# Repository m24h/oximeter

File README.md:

# oximeter
A small oximeter using MAX30102/STC8G1K08A/0.5-inch-OLED/Phase-Detect algorithm

features:

1. SpO2 detection.
2. Heart beat rate detection.
3. With a USB charging interface.
4. Small and cheap.
5. Compatible with Keil C51 or SDCC

!!!IMPORTANT!!!

First thing:
I made an ergonomic mistake in my design, my original idea was to use a button to turn on the power and the sensor underneath would just fit the finger.
But the excessive pressure affected the blood flowing in the finger, also the results.
I suggest that subsequent developers can modify the PCB and box case, use a toggle switche instead of the button, which can be placed on the side of the case, and place the sensor on the same side of the OLED (Top side), So the users can just touch the sensor surface gently by a finger, that would result in fast and accurate detection results.

Second thing:
Hex file for burning/Downloading is included here, TTL serial port is connected to D+/D- pin of USB charging interface, subsequent developers can also try to download hex file directly using pseudo USB downloading port of STC8G1K08A (ID pin of micro-USB port is required to be connected to GND, but I've never tried, and I heard that there is a certain failure rate).
But STC-ISP V6.90 (the STC official downloading software) has an strange BUG, which will cause straightforward downloading to fail.
In my design, I put const parameters like fonts and some tables into EEPROM area (which is indexed from 0x2000), STC-ISP says "This file is over the valid scope, and the exceeding part has been moved to EEPROM area", which looks as expected, BUT it is not. STC-ISP does not split the hex file at 0x2000, but at 0x1FF9.
The workaround for this strange problem is to manually delete first 7 bytes at "EEPROM Buffer" tab-page on the STC-ISP interface, and "Save Buffer" to a .bin file, and re-load the file using "Open EEPROM file", the burn it.

Other downloading things:
IRC frequency is 22.1184MHz.
Don't enable WDT.
Rest pin is used as I/O port.

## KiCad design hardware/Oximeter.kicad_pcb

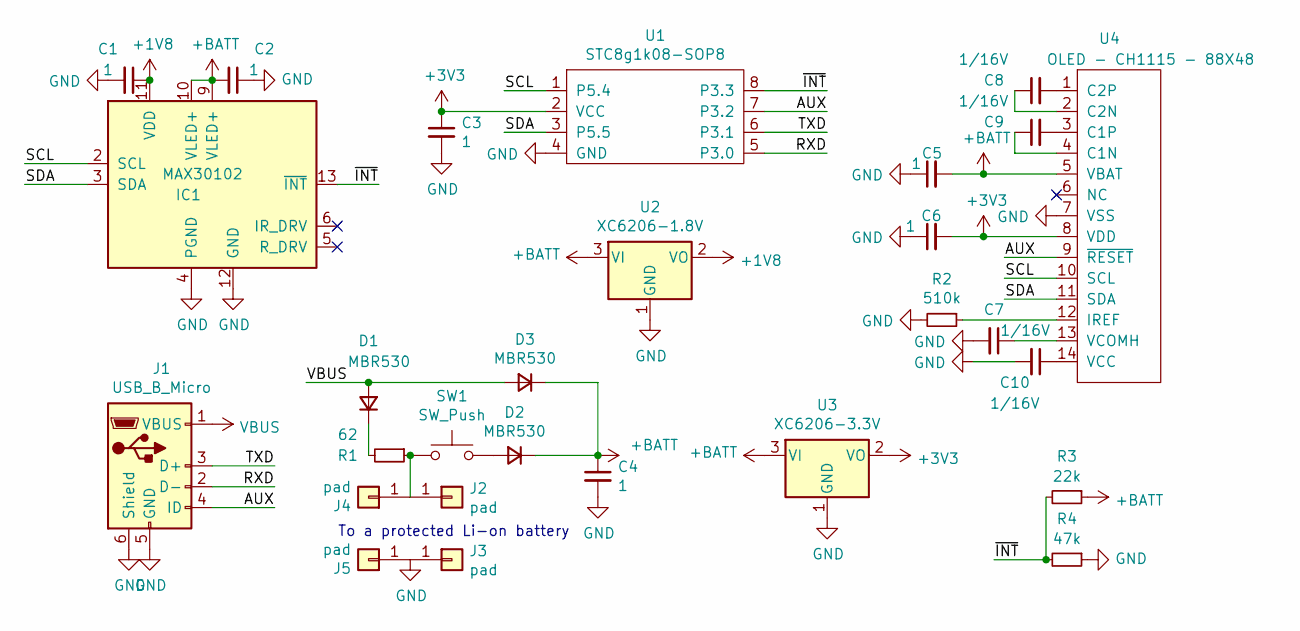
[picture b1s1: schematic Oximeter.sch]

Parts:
C1, C2, C3, C4, C5, C6: 1; C_0603_1608Metric
C7, C8, C9, C10: 1/16V; C_0603_1608Metric
D1, D2, D3: MBR530; D_SOD-123
IC1: MAX30102; Maxim_OLGA-14_3.3x5.6mm_P0.8mm
J1: USB_B_Micro; USB_Micro-B_Molex-105017-0001
J2, J3, J4, J5: pad; Pad-SMD
R1: 62; R_0603_1608Metric
R2: 510k; R_0603_1608Metric
R3: 22k; R_0603_1608Metric
R4: 47k; R_0603_1608Metric
SW1: SW_Push; SW_Push_1P1T_NO_6x6mm_H9.5mm
U1: STC8g1k08-SOP8; SOP-8_3.9x4.9mm_P1.27mm
U2: XC6206-1.8V; SOT-23
U3: XC6206-3.3V; SOT-23
U4: OLED - CH1115 - 88X48; OLED-0.5IN-14PIN

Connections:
+1V8: C1.1, IC1.11 (VDD), U2.2 (VO)
+3V3: C3.1, C6.2, U1.2 (VCC), U3.2 (VO), U4.8 (VDD)
+BATT: C2.2, C4.1, C5.2, D2.1 (K), D3.1 (K), IC1.9 (VLED+), IC1.10 (VLED+), R3.1, U2.3 (VI), U3.3 (VI), U4.5 (VBAT)
/AUX: J1.4 (ID), U1.7 (P3.2), U4.9 (~RESET)
/RXD: J1.2 (D-), U1.5 (P3.0)
/SCL: IC1.2 (SCL), U1.1 (P5.4), U4.10 (SCL)
/SDA: IC1.3 (SDA), U1.3 (P5.5), U4.11 (SDA)
/TXD: J1.3 (D+), U1.6 (P3.1)
/~INT: IC1.13 (~INT), R3.2, R4.2, U1.8 (P3.3)
GND: C1.2, C2.1, C3.2, C4.2, C5.1, C6.1, C7.2, C10.2, IC1.4 (PGND), IC1.12 (GND), J1.5 (GND), J1.6 (Shield), J3.1, J5.1, R2.2, R4.1, U1.4 (GND), U2.1 (GND), U3.1 (GND), U4.7 (VSS)
unnamed: C7.1, U4.13 (VCOMH)
unnamed: C8.1, U4.2 (C2N)
unnamed: C8.2, U4.1 (C2P)
unnamed: C9.1, U4.4 (C1N)
unnamed: C9.2, U4.3 (C1P)
unnamed: C10.1, U4.14 (VCC)
unnamed: D1.1 (K), R1.2
unnamed: D2.2 (A), SW1.2
unnamed: J2.1, J4.1, R1.1, SW1.1
unnamed: R2.1, U4.12 (IREF)
VBUS: D1.2 (A), D3.2 (A), J1.1 (VBUS)

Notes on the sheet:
To a protected Li-on battery

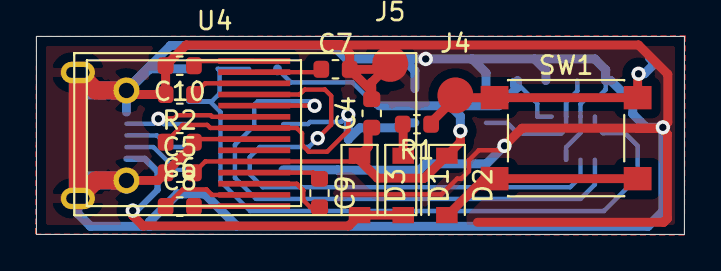
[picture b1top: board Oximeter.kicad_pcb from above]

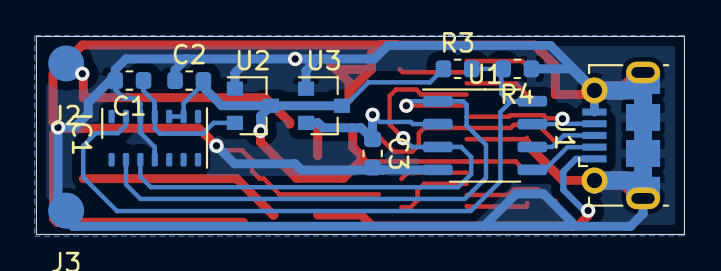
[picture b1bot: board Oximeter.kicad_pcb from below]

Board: 2 copper layers, 36.0 x 11.0 mm, 28 parts (12 on the bottom side), 21 nets.
